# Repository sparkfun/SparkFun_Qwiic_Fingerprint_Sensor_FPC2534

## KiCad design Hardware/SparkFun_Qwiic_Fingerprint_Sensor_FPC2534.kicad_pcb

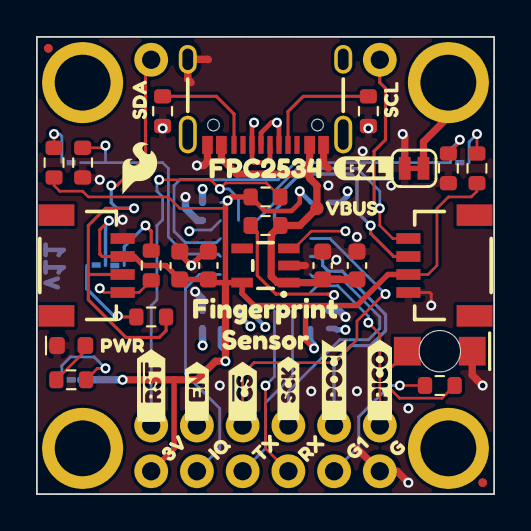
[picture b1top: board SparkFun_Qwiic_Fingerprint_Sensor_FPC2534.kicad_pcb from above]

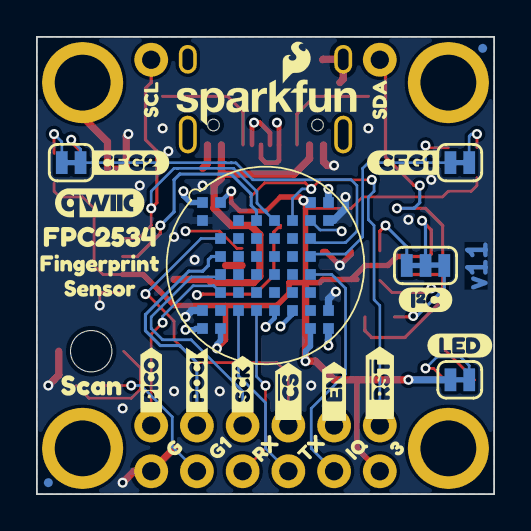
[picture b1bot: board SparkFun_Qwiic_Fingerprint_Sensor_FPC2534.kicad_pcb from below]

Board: 4 copper layers, 25.4 x 25.4 mm, 84 parts (29 on the bottom side), 29 nets.

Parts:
C2, C5: 10uF; C_0603_1608Metric
C3, C4: 1.0uF; C_0603_1608Metric
D1: Red; LED_0603_1608Metric_Red
D2: Green; LED_1206_Bottom_Green
FID1, FID2, FID3, FID4: Fiducial_0.5mm; Fiducial_0.5mm_Mask1mm
G4: OSHW_Logo; Creative_Commons_License
J1, J2: Qwiic_RA; JST_SMD_1.0mm-4_Black
J3, J6: Conn_01x01; 1x01
J4: USB_C_Receptacle; USB-C_16
J5, J7: Conn_01x06; 1x06
JP1: LED; Jumper_2_NC_Trace
JP2: CFG1; Jumper_2_NC_Trace
JP3: CFG2; Jumper_2_NC_Trace
JP4: I2C; Jumper_3_NC-2_Trace
JP5: BZL; Jumper_2_NC_Trace
R1: 10k; R_0603_1608Metric
R2, R4: 5.1k; R_0603_1608Metric
R3: 4.7k; R_0603_1608Metric
R5, R8, R10: 1k; R_0603_1608Metric
R6, R7, R9: 100k; R_0603_1608Metric
R11, R12: 2.2k; R_0603_1608Metric
ST5, ST6, ST7, ST8: Standoff; Standoff_Connected
TP2: TestPoint_0.75mm; TestPoint-0.75mm
U1: FPC2354; FPC253x
U2: RT9080-3.3; SOT23-5
kibuzzard-68A62B00: G***; kibuzzard-68A62B00
kibuzzard-68B211A8: G***; kibuzzard-68B211A8
kibuzzard-68B211AF: G***; kibuzzard-68B211AF
kibuzzard-68B211BC: G***; kibuzzard-68B211BC
kibuzzard-68B211C4: G***; kibuzzard-68B211C4
kibuzzard-68B212A1: G***; kibuzzard-68B212A1
kibuzzard-68B2110A: G***; kibuzzard-68B2110A
kibuzzard-68B2118A: G***; kibuzzard-68B2118A
kibuzzard-68B2127B: G***; kibuzzard-68B2127B
kibuzzard-68B21103: G***; kibuzzard-68B21103
kibuzzard-68B21113: G***; kibuzzard-68B21113
kibuzzard-68B21123: G***; kibuzzard-68B21123
kibuzzard-68B21145: G***; kibuzzard-68B21145
kibuzzard-68B21150: G***; kibuzzard-68B21150
kibuzzard-68B21159: G***; kibuzzard-68B21159
kibuzzard-68B21162, kibuzzard-68B21162#2: G***; kibuzzard-68B21162
kibuzzard-68B21169, kibuzzard-68B21169#2: G***; kibuzzard-68B21169
kibuzzard-68B21179: G***; kibuzzard-68B21179
kibuzzard-68B21181: G***; kibuzzard-68B21181
kibuzzard-68B21196: G***; kibuzzard-68B21196
kibuzzard-68B21259: G***; kibuzzard-68B21259
kibuzzard-68B21262: G***; kibuzzard-68B21262
kibuzzard-68B21280: G***; kibuzzard-68B21280
kibuzzard-68B21331: G***; kibuzzard-68B21331
kibuzzard-68BB5A49: G***; kibuzzard-68BB5A49
kibuzzard-68BB5B7A: G***; kibuzzard-68BB5B7A
kibuzzard-68BB5B8B: G***; kibuzzard-68BB5B8B
kibuzzard-68BB5B69: G***; kibuzzard-68BB5B69
kibuzzard-68BB5B72: G***; kibuzzard-68BB5B72
kibuzzard-68BB5B86: G***; kibuzzard-68BB5B86
kibuzzard-68BB5BA4: G***; kibuzzard-68BB5BA4
kibuzzard-68BB5BAA: G***; kibuzzard-68BB5BAA
kibuzzard-68BB5BB0: G***; kibuzzard-68BB5BB0
kibuzzard-68BB5BE0: G***; kibuzzard-68BB5BE0
kibuzzard-68BB5BFB: G***; kibuzzard-68BB5BFB
kibuzzard-68C08F5C: G***; kibuzzard-68C08F5C
kibuzzard-68C08F6E, kibuzzard-68C08F6E#2: G***; kibuzzard-68C08F6E
kibuzzard-68C08FA6: G***; kibuzzard-68C08FA6
kibuzzard-68C0923F: G***; kibuzzard-68C0923F

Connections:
3.3V: C4.1, C5.1, J1.2, J2.2, J7.1, JP1.2 (B), JP4.2 (B), R1.2, R5.2, R8.2, U1.A2 (3V3), U1.A7 (3V3), U1.H2 (3V3), U1.H7 (3V3), U2.5 (VOUT)
CFG1: JP2.1 (A), R6.2, U1.D7 (IF_CFG_1)
CFG2: JP3.1 (A), R7.2, U1.C7 (IF_CFG_2)
DM: J4.A7 (D-), J4.B7 (D-), U1.G5 (DM)
DP: J4.A6 (D+), J4.B6 (D+), U1.G6 (DP)
EGND: JP5.1 (A), ST5.1, ST6.1, ST7.1, ST8.1, U1.A1 (EGND), U1.A8 (EGND), U1.H1 (EGND), U1.H8 (EGND)
EN: J5.2, R9.1, U2.3 (EN)
GND: C2.2, C3.2, C4.2, C5.2, D1.1 (K), D2.1 (K), J1.1, J2.1, J4.GND, J4.S (SHIELD), J7.6, JP5.2 (B), R2.1, R4.1, R6.1, R7.1, U1.B1 (GND), U1.B8 (GND), U1.G1 (GND), U1.G8 (GND), U2.2 (GND)
GPIO1: J7.5, R10.2, U1.B7 (GPIO1)
IRQ: J7.2, U1.E7 (IRQ)
unnamed: D1.2 (A), R3.1
unnamed: D2.2 (A), R10.1
unnamed: J4.A5 (CC1), R4.2
unnamed: J4.B5 (CC2), R2.2
unnamed: JP1.1 (A), R3.2
unnamed: JP2.2 (B), R5.1
unnamed: JP3.2 (B), R8.1
unnamed: JP4.1 (A), R12.2
unnamed: JP4.3 (C), R11.2
PICO: J5.6, U1.F2 (PICO)
POCI: J5.5, U1.D2 (POCI)
RX: J7.4, U1.G4 (RX)
SCK: J5.4, U1.E2 (SCK)
SCL: J1.4, J2.4, J3.1, R12.1, U1.B5 (SCL)
SDA: J1.3, J2.3, J6.1, R11.1, U1.B4 (SDA)
TX: J7.3, U1.G3 (TX)
VBUS: C2.1, C3.1, J4.VBUS, R9.2, TP2.1, U2.1 (VIN)
~CS: J5.3, U1.C2 (~CS)
~RST: J5.1, R1.1, U1.B6 (~RST)

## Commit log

2025-08-29 Add I2C pull ups and jumper. Adjust silk.
2025-09-09 Post design review.
2025-09-09 Add panel files
2025-09-09 Roll PCB version forward
2025-12-04 Initial docs review
    Adding GitHub pages documentation files after initial review to prep for GH pages publish.
2025-12-04 Final Review and build files
    Final review edits and build files to publish docs.
2025-12-04 Deployed c2f112e with MkDocs version: 1.6.1
2026-06-03 Deployed 7282e3e with MkDocs version: 1.6.1

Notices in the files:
parts and their libraries:
https://creativecommons.org/licenses/by-sa/4.0
Released under the Creative Commons Attribution Share-Alike 4.0 License
